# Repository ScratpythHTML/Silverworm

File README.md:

# Silverworm
Hardware and software design for the Silverworm spiral yarn wrapping machine.

## Group A
This is the wrapping team. We have designed a rotating arm that enscapulates a core yarn with a conductive outer fibre. The code in this repository is used to set the speed of the motor.

### Hardware
- Arduino Nano Every
- VNH5019 Motor Driver
- Honeywell Digital Hall Effect Sensor
- CHANCS 30W Permanent Magnet DC Motor 

### Software
The arduino code takes an inputted reference speed and accelerates the motor to this. It uses a Hall effect sensor and magnets on the arm to calculate the current speed. A PID controller is used for this system to eliminate error and ensure the motor willl get to the correct speed with in a set time. 

## Group B
This is the feeding. We have a feeding system that is passively tensioned which goes into team A's system; after the warpped yarn comes out, we collect it on a rotating collecting spool, which is on a linear rail to ensure orthodirectionality. 

### Hardware
- STM32
- DM423T Stepper Driver
- Linear Guide Rail with Nema 23 Stepper Motor
- oDrive S1 Motor Driver
- 24V 3000RPM 0.16Nm 50W 3.30A 42x42x62mm Brushless DC Motor ( with included hall effect sensor ) 
- 2 x Incremental Rotary Encoder IHC3808-001G-2000BZ1 ABZ 3-Channel 8mm Hollow Shaft

### Software
The code would take a inputted speed of the linear core yarn and then calculate the corresponding speeds that the linear rail and the BLDC motor would need to run at to ensure linear speed is accurate. The 2 encoders would give us both the radial velocity of the wrapper and the core yarn, allowing us to create a closed-loop control.

## Group C
This is the integration & control software — a PyQt6 app on a Raspberry Pi that reads the physical control panel, drives both motors, and measures yarn pitch live from a microscope camera.

### Hardware
- Raspberry Pi (Compute Module 5 + IO board)
- ESP32 physical UI panel — dials + mode/power switches (I2C)
- Wrap & feed motor controllers (SPI)
- AmScope HHD 8300-P USB microscope

### Software
The app is the system's central controller. It holds the machine state (mode, power, wrap + feed speeds), and the **physical panel is always the source of truth** — GUI controls are overwritten by the next dial/switch input. In AUTO it measures wrap pitch from the live camera and adjusts feed speed to hit the target; in MANUAL it overlays the target pitch/angle on the camera view for hand setup.

### Quick start

**On the wrapping machine (Raspberry Pi):**
```bash
python3 -m pip install -r interface/requirements-rpi.txt --break-system-packages
cd interface && python3 app.py
```

**On another computer (development, no hardware):**
```bash
python3 -m pip install -r interface/requirements.txt
cd interface && python3 app.py
```

On first launch you'll set target pitch, wire thickness, and tube diameter (tick "Remember settings" to skip it next time). With no panel attached, use the **Debug** menu to simulate dial/switch input.

### Code files
```
interface/
  app.py             Launcher — startup dialog → main window
  ui/main_window.py  Wires UI + state + hardware together
  app_state.py       Central state (mode/power/speeds), routes motor commands
  config.py          Settings, JSON persistence, wrap-angle math
  pitch_control.py   Closed-loop pitch → feed-speed control
  telemetry.py       Per-command timing/telemetry for the test report
  storage.py         Atomic saves (snapshots, recordings, logs)
  hardware.py        Picks real vs mock I2C/SPI transports per platform
  comms/
    pui.py           ESP32 panel protocol (I2C parser + listener)
    motor_spi.py     Arduino motor protocol (SPI packet codec)
  camera/            AmScope detection, capture, rolling frame buffer
  processing/
    pipeline.py      Runs pitch estimation on live camera frames
  ui/                GUI widgets (camera view, controls, graphs, dialogs)
  hil_test.py        Hardware-in-the-loop harness (no camera needed)
  diagnose.py        Environment / setup checker
image-processing/
  pitch_estimate.py  CV pitch measurement (OpenCV + SciPy)
```

### Continuing development
Start at `app.py` → `ui/main_window.py` → `app_state.py` (the central state machine). The reference sections below cover the protocols, formulas, and extension recipes you need to add features or bring up new hardware.

## How it works (reference)

### Architecture
```
ESP32 (panel) ──I2C──► Raspberry Pi (this app) ──SPI──► Arduino (motors)
 dials/switches          PyQt6 GUI + vision            wrap + feed
                         AppState = source of truth
```
The **physical panel always wins**: any dial/switch event overwrites what the GUI set. The GUI is a display/backup.

### Communication protocols
**I2C — panel → Pi (ASCII):**

| Message | Meaning |
|---|---|
| `D1±N` | Dial 1 (wrap) ± N detents, N∈{1,2,3} = small/med/large |
| `D2±N` | Dial 2 (feed) ± N detents |
| `AS0` / `AS1` | Mode → MANUAL / AUTO |
| `TP` | Toggle machine power |

Dials send *increments*, not absolute values; the detent→units lookup is in `DetentConfig` (`config.py`).

**SPI — Pi → Arduino (byte packets):**

| Prefix | Command | Payload |
|--------|---------|---------|
| `0x01` | Start | speedL, speedH (uint16 LE) |
| `0x02` | Stop | stop_type (1=ramp, 2=emergency, 3=power-off) |
| `0x03` | Set speed | speedL, speedH |
| `0x04` | Test movement | movement_type |
| `0x05` | Request speed | — |

**SPI — Arduino → Pi:** `0x01` current speed · `0x02` error_code · `0x03` sequence status.

### Core formulas
```python
theta = arctan(pitch / (pi * (tube_diameter + 2 * wire_thickness)))  # wrap angle
pitches_um = np.diff(peak_positions_px) * um_per_px                   # pitch from peaks
cv = std_pitch / mean_pitch                                          # confidence:
#   HIGH if wraps>=10 and cv<0.20 ; MEDIUM if wraps>=5 and cv<0.35 ; else LOW
```

### Settings
Persisted to the OS config dir, loaded on startup (target pitch, wire thickness, tube diameter, detent→speed mappings, remember-settings): macOS `~/Library/Preferences/Silverworm/config.json`, Linux `~/.config/Silverworm/config.json`. The manual-mode GUI toggle is hidden by default (enable in Settings with the warning ack) to avoid PUI/GUI desync.

## Extending the app
- **New PUI message:** add a case in `parse_pui_message()` + a dataclass (`comms/pui.py`) → signal on `PUIListener` → `apply_*` handler on `AppState` → wire in `MainWindow._connect_app_state_signals()` → test in `tests/test_pui_protocol.py` + `tests/test_app_state.py`.
- **New motor command:** add to `CommandPrefix` + `build_<cmd>()` with bounds checks (`comms/motor_spi.py`) → method on `MotorController` → test in `tests/test_motor_spi.py`.
- **Tune pitch detection:** edit `image-processing/pitch_estimate.py` (`min_dist_px`, `sigma`, `prom_factor`).

## Testing
```bash
cd interface
pytest -q tests/test_pui_protocol.py tests/test_motor_spi.py tests/test_app_state.py
```
The protocol layer is fully tested without hardware via `MockPUITransport` / `MockSPITransport`. Camera/UI tests need Linux + `pytest-qt`.

## Repository map
Several subfolders have their own README with hardware-specific detail (pin maps, wiring, board files). Start here, then drill in:

| Folder | Contents |
|--------|----------|
| [interface/](interface/) | Group C control software (see above) |
| [image-processing/](image-processing/) | Pitch-measurement CV pipeline |
| [GroupA/](GroupA/) | Group A wrapper-motor firmware (Arduino Nano Every) |
| [GroupB/](GroupB/README.md) | Group B collecting firmware + Uno pin map |
| [IO Panel/](IO%20Panel/Silverworm_Control_Panel/README.md) | ESP32 panel pinout + I2C protocol |
| → [Web test tool](IO%20Panel/Silverworm_Control_Panel/IO%20Panel%20Software/Web_Test_Version/README.md) | Browser serial test UI for the panel |
| [Motherboard/Hardware/](Motherboard/Hardware/Silverworm%20-%20CM5%20Motherboard/) | CM5 carrier-board KiCAD files |
| [Motherboard/Software/](Motherboard/Software/README.md) | Enabling SPI/I2C on the CM5 |
| [Subsystem Interfacing/](Subsystem%20Interfacing/README.md) | Cross-board SPI wiring overview |

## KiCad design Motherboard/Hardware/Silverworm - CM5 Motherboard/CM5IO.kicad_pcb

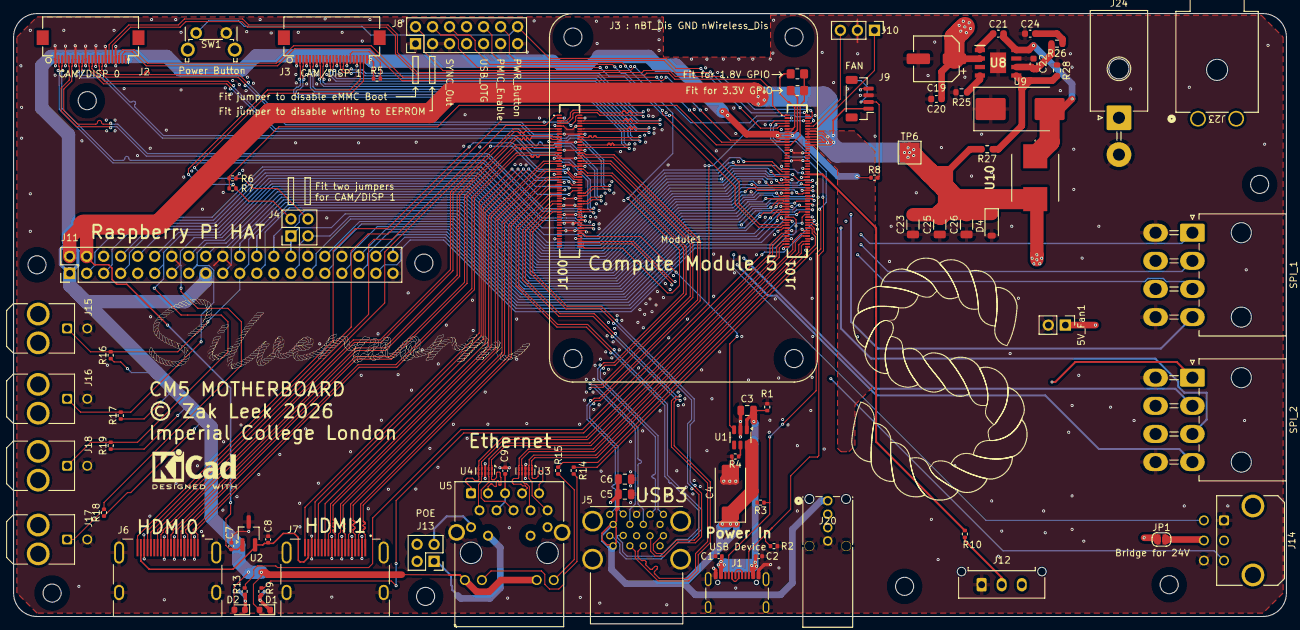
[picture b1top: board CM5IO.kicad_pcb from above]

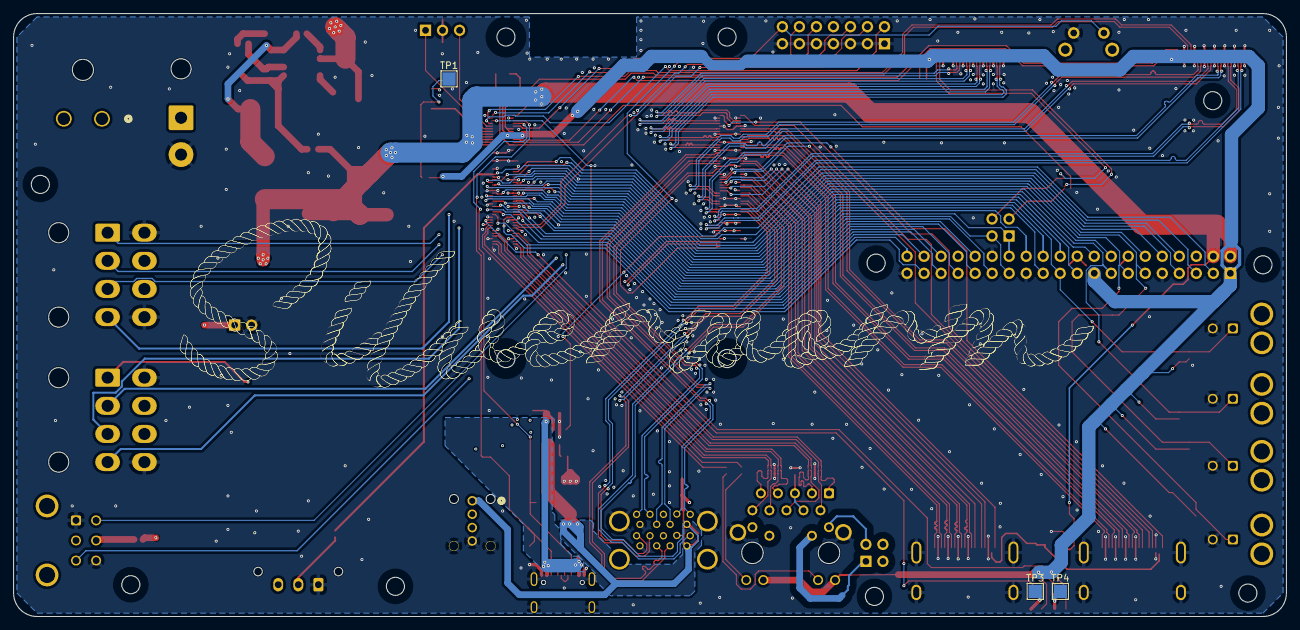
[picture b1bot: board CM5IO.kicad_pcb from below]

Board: 4 copper layers, 190.0 x 90.0 mm, 92 parts (3 on the bottom side), 148 nets.

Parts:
5V_Fan1: 1x2 Pin Header; PinHeader_1x02_P2.54mm_Vertical
C1, C2, C7, C8, C9: 100n; C_0402_1005Metric
C3, C5, C6: 10u; C_0805_2012Metric
C4: 100uF; CP_EIA-7343-31_Kemet-D
C19: GVT1J476M0608CNVC; CP_Elec_6.3x7.7
C20, C21: 100nF; C_0603_1608Metric
C22: 68pF; C_0603_1608Metric
C23, C25, C26: 47uF; C_1206_3216Metric
C24: 22nF; C_0603_1608Metric
D1: LED Green; LED_0603_1608Metric
D2: LED Red; LED_0603_1608Metric
D4: SMFJ5.0A; D_SOD-123
H1, H2, H3, H4, H5, H6, H7, H8: MountingHole; MountingHole_2.7mm_M2.5_DIN965
J1: USB_C_Receptacle_USB2.0; USB_C_Receptacle_GCT_USB4105-xx-A_16P_TopMnt_Horizontal
J2, J3: Conn_01x22_Female; Hirose_FH12-22S-0.5SH_1x22-1MP_P0.50mm_Horizontal
J4, J13: THD-02-R; PinHeader_2x02_P2.54mm_Vertical
J5: USB3_A; MTCONN_UBAF30-D2011
J6, J7: 690-019-298-412; EDAC 690-019-298-412
J8: Conn_02x07_Odd_Even; PinHeader_2x07_P2.54mm_Vertical
J9: JST_SHBM04B-SRSS-TB; JST_SH_BM04B-SRSS-TB_1x04-1MP_P1.00mm_Vertical
J10: Conn_01x03; PinHeader_1x03_P2.54mm_Vertical
J11: THD-20-R; PinHeader_2x20_P2.54mm_Vertical
J12: Microfit 3-pin; Molex_Micro-Fit_3.0_43650-0315_1x03_P3.00mm_Vertical
J14: Microfit 6-pin; Molex_Micro-Fit_3.0_43045-0621_2x03-1MP_P3.00mm_Horizontal
J15, J16, J17, J18: Microfit 2-Pin; Molex_Micro-Fit_3.0_43045-0221_2x01-1MP_P3.00mm_Horizontal
J20: USB_A; CONN_48204-0001_MOL
J23: Mega-Fit-1row-2pin; CONN_2002412000_02_MOL
J24: Mega-Fit-2row-2pin; Molex_Mega-Fit_76825-0002_2x01_P5.70mm_Horizontal
J100, J101: 101642271001A1RLF
JP1: Jumper_2_Open; SolderJumper-2_P1.3mm_Open_RoundedPad1.0x1.5mm
Module1: ComputeModule5-CM5; Raspberry-Pi-5-Compute-Module
R1, R5, R6, R7: 2.2K 1%; R_0402_1005Metric
R2, R3: 5.1K; R_0402_1005Metric
R4: 15K 1%; R_0402_1005Metric
R8: 10K 1%; R_0402_1005Metric
R9, R13: 1k; R_0402_1005Metric
R10, R14, R15: 470R; R_0402_1005Metric
R11: 0R; R_0805_2012Metric_Pad1.20x1.40mm_HandSolder
R12: nf; R_0805_2012Metric_Pad1.20x1.40mm_HandSolder
R16, R17, R18, R19: 10K; R_0402_1005Metric
R25: 120k; R_0603_1608Metric
R26, R28: 10k; R_0603_1608Metric
R27: 51k; R_0603_1608Metric
SPI_1, SPI_2: Minifit 2x4; Molex_Mini-Fit_Jr_5569-08A2_2x04_P4.20mm_Horizontal
SW1: Right angle Tact button; SW_Tactile_SPST_Angled_PTS645Vx58-2LFS
TP1, TP3, TP4: TestPoint; TestPoint_Pad_2.0x2.0mm
TP6: +5V; TestPoint_Pad_3.0x3.0mm
U1: AP22653W6; SOT-23-6
U2: RT9742SNGV; TSOT-23_HandSoldering
U3, U4: TPD4EUSB30; USON-10_2.5x1.0mm_P0.5mm
U5: MagJack-A70-112-331N126; TRJG0926HENL
U8: TPS54560DDAR; SOIC127P600X170-9N
U9: SS54; D_SMC_Handsoldering
U10: 10uH; ETQP5M_YFM

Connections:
24V_INPUT: J23.1, J24.1
+5V: 5V_Fan1.1, C1.1, C2.1, C3.1, C7.1, C23.2, C25.2, C26.2, D4.1 (K), J1.A4 (VBUS), J1.A9 (VBUS), J1.B4 (VBUS), J1.B9 (VBUS), J9.1, J11.2, J11.4, J12.3, J14.2, Module1.77 (+5v_(Input)), Module1.79 (+5v_(Input)), Module1.81 (+5v_(Input)), Module1.83 (+5v_(Input)), Module1.85 (+5v_(Input)), Module1.87 (+5v_(Input)), R1.2, R27.2, SPI_1.7, SPI_2.7, TP6.1, U1.1 (IN), U2.1 (IN), U10.2
+24V: C19.1, C20.1, J23.2, JP1.1 (A), SPI_1.6, SPI_2.6, U8.2 (VIN)
/+3.3v: D1.2 (A), D2.2 (A), J11.1, J11.17, Module1.84 (+3.3v_(Output)), Module1.86 (+3.3v_(Output)), R8.1, R11.1, R16.1, R17.1, R18.1, R19.1, U5.15 (LEDY_A), U5.17 (LEDG_A)
/CC1: J1.A5 (CC1), Module1.94 (CC1), R3.1
/CC2: J1.B5 (CC2), Module1.96 (CC2), R2.1
/CM5_GPIO ( Ethernet, GPIO, SDCARD)/+1.8v: Module1.88 (+1.8v_(Output)), Module1.90 (+1.8v_(Output)), R12.1
/CM5_GPIO ( Ethernet, GPIO, SDCARD)/BT_nDis: J10.3, Module1.91 (BT_nDisable)
/CM5_GPIO ( Ethernet, GPIO, SDCARD)/CAM_GPIO0: J2.17, Module1.97 (CAM_GPIO0)
/CM5_GPIO ( Ethernet, GPIO, SDCARD)/CAM_GPIO1: J2.18, Module1.100 (CAM_GPIO1)
/CM5_GPIO ( Ethernet, GPIO, SDCARD)/CSn_1: Module1.49 (GPIO18), SPI_1.4
/CM5_GPIO ( Ethernet, GPIO, SDCARD)/CSn_3: Module1.54 (GPIO4), SPI_2.4
/CM5_GPIO ( Ethernet, GPIO, SDCARD)/EEPROM_nWP: J8.4, Module1.20 (EEPROM_nWP)
/CM5_GPIO ( Ethernet, GPIO, SDCARD)/ETH_LEDG: Module1.17 (Ethernet_nLED2(3.3v)), R14.2
/CM5_GPIO ( Ethernet, GPIO, SDCARD)/ETH_LEDY: Module1.15 (Ethernet_nLED3(3.3v)), R15.2
/CM5_GPIO ( Ethernet, GPIO, SDCARD)/GPIO2: J11.3, Module1.58 (GPIO2)
/CM5_GPIO ( Ethernet, GPIO, SDCARD)/GPIO3: J11.5, Module1.56 (GPIO3)
/CM5_GPIO ( Ethernet, GPIO, SDCARD)/GPIO8: J11.24, Module1.39 (GPIO8)
/CM5_GPIO ( Ethernet, GPIO, SDCARD)/GPIO9: J11.21, J15.1, Module1.40 (GPIO9), R16.2
/CM5_GPIO ( Ethernet, GPIO, SDCARD)/GPIO10: J11.19, J14.4, Module1.44 (GPIO10)
/CM5_GPIO ( Ethernet, GPIO, SDCARD)/GPIO11: J11.23, J14.3, Module1.38 (GPIO11)
/CM5_GPIO ( Ethernet, GPIO, SDCARD)/GPIO12: J11.32, Module1.31 (GPIO12)
/CM5_GPIO ( Ethernet, GPIO, SDCARD)/GPIO13: J11.33, Module1.28 (GPIO13)
/CM5_GPIO ( Ethernet, GPIO, SDCARD)/GPIO15: J11.10, Module1.51 (GPIO15)
/CM5_GPIO ( Ethernet, GPIO, SDCARD)/GPIO16: J11.36, Module1.29 (GPIO16)
/CM5_GPIO ( Ethernet, GPIO, SDCARD)/GPIO23: J11.16, Module1.47 (GPIO23)
/CM5_GPIO ( Ethernet, GPIO, SDCARD)/GPIO24: J11.18, Module1.45 (GPIO24)
/CM5_GPIO ( Ethernet, GPIO, SDCARD)/GPIO25: J11.22, Module1.41 (GPIO25)
/CM5_GPIO ( Ethernet, GPIO, SDCARD)/GPIO26: J11.37, Module1.24 (GPIO26)
/CM5_GPIO ( Ethernet, GPIO, SDCARD)/GPIO_VREF: Module1.78 (GPIO_VREF(1.8v/3.3v_Input)), R6.1, R7.1, R11.2, R12.2
/CM5_GPIO ( Ethernet, GPIO, SDCARD)/ID_SC: J4.1, J11.28, Module1.35 (ID_SC)
/CM5_GPIO ( Ethernet, GPIO, SDCARD)/ID_SD: J4.3, J11.27, Module1.36 (ID_SD)
/CM5_GPIO ( Ethernet, GPIO, SDCARD)/LED_DATA: Module1.55 (GPIO14), R10.1
/CM5_GPIO ( Ethernet, GPIO, SDCARD)/LK_2: J16.1, Module1.46 (GPIO22), R17.2
/CM5_GPIO ( Ethernet, GPIO, SDCARD)/LK_3: J17.1, Module1.48 (GPIO27), R18.2
/CM5_GPIO ( Ethernet, GPIO, SDCARD)/LK_4: J18.1, Module1.50 (GPIO17), R19.2
/CM5_GPIO ( Ethernet, GPIO, SDCARD)/MISO_1: Module1.26 (GPIO19), SPI_1.2
/CM5_GPIO ( Ethernet, GPIO, SDCARD)/MISO_3: Module1.34 (GPIO5), SPI_2.2
/CM5_GPIO ( Ethernet, GPIO, SDCARD)/MOSI_1: Module1.27 (GPIO20), SPI_1.1
/CM5_GPIO ( Ethernet, GPIO, SDCARD)/MOSI_3: Module1.30 (GPIO6), SPI_2.1
/CM5_GPIO ( Ethernet, GPIO, SDCARD)/PMIC_ENABLE: J8.12, Module1.99 (PMIC_ENABLE)
/CM5_GPIO ( Ethernet, GPIO, SDCARD)/PWM: J9.2, Module1.19 (FAN_PWM), R8.2, TP1.1
/CM5_GPIO ( Ethernet, GPIO, SDCARD)/PWR_BUT: J8.14, Module1.92 (PWR_BUT), SW1.1
/CM5_GPIO ( Ethernet, GPIO, SDCARD)/SCLK_1: Module1.25 (GPIO21), SPI_1.3
/CM5_GPIO ( Ethernet, GPIO, SDCARD)/SCLK_3: Module1.37 (GPIO7), SPI_2.3
/CM5_GPIO ( Ethernet, GPIO, SDCARD)/SYNC_OUT: J8.6, Module1.18 (Ethernet_SYNC_OUT(3.3v))
/CM5_GPIO ( Ethernet, GPIO, SDCARD)/TACHO: J9.4, Module1.16 (FAN_TACHO)
/CM5_GPIO ( Ethernet, GPIO, SDCARD)/TR0_TAP: J13.3, U5.11 (VC1)
/CM5_GPIO ( Ethernet, GPIO, SDCARD)/TR1_TAP: J13.1, U5.12 (VC2)
/CM5_GPIO ( Ethernet, GPIO, SDCARD)/TR2_TAP: J13.2, U5.13 (VC3)
/CM5_GPIO ( Ethernet, GPIO, SDCARD)/TR3_TAP: J13.4, U5.14 (VC4)
/CM5_GPIO ( Ethernet, GPIO, SDCARD)/TRD0_N: Module1.10 (Ethernet_Pair0_N), U4.4 (D2+), U4.7, U5.2 (TRD0-)
/CM5_GPIO ( Ethernet, GPIO, SDCARD)/TRD0_P: Module1.12 (Ethernet_Pair0_P), U4.5 (D2-), U4.6, U5.1 (TRD0+)
/CM5_GPIO ( Ethernet, GPIO, SDCARD)/TRD1_N: Module1.6 (Ethernet_Pair1_N), U4.2 (D1-), U4.9, U5.6 (TRD1-)
/CM5_GPIO ( Ethernet, GPIO, SDCARD)/TRD1_P: Module1.4 (Ethernet_Pair1_P), U4.1 (D1+), U4.10, U5.3 (TRD1+)
/CM5_GPIO ( Ethernet, GPIO, SDCARD)/TRD2_N: Module1.9 (Ethernet_Pair2_N), U3.4 (D2+), U3.7, U5.8 (TRD2-)
/CM5_GPIO ( Ethernet, GPIO, SDCARD)/TRD2_P: Module1.11 (Ethernet_Pair2_P), U3.5 (D2-), U3.6, U5.7 (TRD2+)
/CM5_GPIO ( Ethernet, GPIO, SDCARD)/TRD3_N: Module1.5 (Ethernet_Pair3_N), U3.2 (D1-), U3.9, U5.10 (TRD3-)
/CM5_GPIO ( Ethernet, GPIO, SDCARD)/TRD3_P: Module1.3 (Ethernet_Pair3_P), U3.1 (D1+), U3.10, U5.9 (TRD3+)
/CM5_GPIO ( Ethernet, GPIO, SDCARD)/USBOTG: J8.10, Module1.101 (USB_OTG_ID)
/CM5_GPIO ( Ethernet, GPIO, SDCARD)/WL_nDis: J10.1, Module1.89 (WiFi_nDisable)
/CM5_GPIO ( Ethernet, GPIO, SDCARD)/nPWR_LED: Module1.95 (LED_nPWR), R13.2
/CM5_GPIO ( Ethernet, GPIO, SDCARD)/nRPIBOOT: J8.2, Module1.93 (nRPIBOOT)
/CM5_HighSpeed/+3.3v: J2.22, J3.22, R5.1
/CM5_HighSpeed/DPHY0_C_N: J2.8, Module1.127 (MIPI0_C_N)
/CM5_HighSpeed/DPHY0_C_P: J2.9, Module1.129 (MIPI0_C_P)
/CM5_HighSpeed/DPHY0_D0_N: J2.2, Module1.115 (MIPI0_D0_N)
/CM5_HighSpeed/DPHY0_D0_P: J2.3, Module1.117 (MIPI0_D0_P)
/CM5_HighSpeed/DPHY0_D1_N: J2.5, Module1.121 (MIPI0_D1_N)
/CM5_HighSpeed/DPHY0_D1_P: J2.6, Module1.123 (MIPI0_D1_P)
/CM5_HighSpeed/DPHY0_D2_N: J2.11, Module1.133 (MIPI0_D2_N)
/CM5_HighSpeed/DPHY0_D2_P: J2.12, Module1.135 (MIPI0_D2_P)
/CM5_HighSpeed/DPHY0_D3_N: J2.14, Module1.139 (MIPI0_D3_N)
/CM5_HighSpeed/DPHY0_D3_P: J2.15, Module1.141 (MIPI0_D3_P)
/CM5_HighSpeed/DPHY1_C_N: J3.8, Module1.187 (MIPI1_C_N)
/CM5_HighSpeed/DPHY1_C_P: J3.9, Module1.189 (MIPI1_C_P)
/CM5_HighSpeed/DPHY1_D0_N: J3.2, Module1.175 (MIPI1_D0_N)
/CM5_HighSpeed/DPHY1_D0_P: J3.3, Module1.177 (MIPI1_D0_P)
/CM5_HighSpeed/DPHY1_D1_N: J3.5, Module1.181 (MIPI1_D1_N)
/CM5_HighSpeed/DPHY1_D1_P: J3.6, Module1.183 (MIPI1_D1_P)
/CM5_HighSpeed/DPHY1_D2_N: J3.11, Module1.193 (MIPI1_D2_N)
/CM5_HighSpeed/DPHY1_D2_P: J3.12, Module1.195 (MIPI1_D2_P)
/CM5_HighSpeed/DPHY1_D3_N: J3.14, Module1.194 (MIPI1_D3_N)
/CM5_HighSpeed/DPHY1_D3_P: J3.15, Module1.196 (MIPI1_D3_P)
/CM5_HighSpeed/HDMI0_CEC: J6.13 (CEC), Module1.151 (HDMI0_CEC)
/CM5_HighSpeed/HDMI0_CK_N: J6.12 (CK-), Module1.190 (HDMI0_CLK_N)
/CM5_HighSpeed/HDMI0_CK_P: J6.10 (CK+), Module1.188 (HDMI0_CLK_P)
/CM5_HighSpeed/HDMI0_D0_N: J6.9 (D0-), Module1.184 (HDMI0_TX0_N)
/CM5_HighSpeed/HDMI0_D0_P: J6.7 (D0+), Module1.182 (HDMI0_TX0_P)
/CM5_HighSpeed/HDMI0_D1_N: J6.6 (D1-), Module1.178 (HDMI0_TX1_N)
/CM5_HighSpeed/HDMI0_D1_P: J6.4 (D1+), Module1.176 (HDMI0_TX1_P)
/CM5_HighSpeed/HDMI0_D2_N: J6.3 (D2-), Module1.172 (HDMI0_TX2_N)
/CM5_HighSpeed/HDMI0_D2_P: J6.1 (D2+), Module1.170 (HDMI0_TX2_P)
/CM5_HighSpeed/HDMI0_HOTPLUG: J6.19 (HPD/HEAC-), Module1.153 (HDMI0_HOTPLUG)
/CM5_HighSpeed/HDMI0_SCL: J6.15 (SCL), Module1.200 (HDMI0_SCL)
/CM5_HighSpeed/HDMI0_SDA: J6.16 (SDA), Module1.199 (HDMI0_SDA)
/CM5_HighSpeed/HDMI1_CEC: J7.13 (CEC), Module1.149 (HDMI1_CEC)
/CM5_HighSpeed/HDMI1_CK_N: J7.12 (CK-), Module1.166 (HDMI1_CLK_N)
/CM5_HighSpeed/HDMI1_CK_P: J7.10 (CK+), Module1.164 (HDMI1_CLK_P)
/CM5_HighSpeed/HDMI1_D0_N: J7.9 (D0-), Module1.160 (HDMI1_TX0_N)
/CM5_HighSpeed/HDMI1_D0_P: J7.7 (D0+), Module1.158 (HDMI1_TX0_P)
/CM5_HighSpeed/HDMI1_D1_N: J7.6 (D1-), Module1.154 (HDMI1_TX1_N)
/CM5_HighSpeed/HDMI1_D1_P: J7.4 (D1+), Module1.152 (HDMI1_TX1_P)
/CM5_HighSpeed/HDMI1_D2_N: J7.3 (D2-), Module1.148 (HDMI1_TX2_N)
/CM5_HighSpeed/HDMI1_D2_P: J7.1 (D2+), Module1.146 (HDMI1_TX2_P)
/CM5_HighSpeed/HDMI1_HOTPLUG: J7.19 (HPD/HEAC-), Module1.143 (HDMI1_HOTPLUG)
/CM5_HighSpeed/HDMI1_SCL: J7.15 (SCL), Module1.147 (HDMI1_SCL)
/CM5_HighSpeed/HDMI1_SDA: J7.16 (SDA), Module1.145 (HDMI1_SDA)
/CM5_HighSpeed/HDMI_5v: C8.1, J6.18 (+5V), J7.18 (+5V), U2.2 (OUT)
/CM5_HighSpeed/SCL0: J2.20, Module1.80 (SCL0)
/CM5_HighSpeed/SCL1: J3.20, J4.2, R7.2
/CM5_HighSpeed/SDA0: J2.21, Module1.82 (SDA0)
/CM5_HighSpeed/SDA1: J3.21, J4.4, R6.2
/CM5_HighSpeed/USB2_N: J20.2 (D-), Module1.103 (USB2_N)
/CM5_HighSpeed/USB2_P: J20.3 (D+), Module1.105 (USB2_P)
/CM5_HighSpeed/USB3-0-D_N: J5.A2 (D-), Module1.136 (USB3-0-D_N)
/CM5_HighSpeed/USB3-0-D_P: J5.A3 (D+), Module1.134 (USB3-0-D_P)
/CM5_HighSpeed/USB3-0-RX_N: J5.A6 (SSRX+), Module1.128 (USB3-0-RX_N)
/CM5_HighSpeed/USB3-0-RX_P: J5.A5 (SSRX-), Module1.130 (USB3-0-RX_P)
/CM5_HighSpeed/USB3-0-TX_N: J5.A9 (SSTX+), Module1.140 (USB3-0-TX_N)
/CM5_HighSpeed/USB3-0-TX_P: J5.A8 (SSTX-), Module1.142 (USB3-0-TX_P)
/CM5_HighSpeed/USB3-1-D_N: J5.B2 (D-), Module1.165 (USB3-1-D_N)
/CM5_HighSpeed/USB3-1-D_P: J5.B3 (D+), Module1.163 (USB3-1-D_P)
/CM5_HighSpeed/USB3-1-RX_N: J5.B6 (SSRX+), Module1.157 (USB3-1-RX_N)
/CM5_HighSpeed/USB3-1-RX_P: J5.B5 (SSRX-), Module1.159 (USB3-1-RX_P)
/CM5_HighSpeed/USB3-1-TX_N: J5.B9 (SSTX+), Module1.169 (USB3-1-TX_N)
/CM5_HighSpeed/USB3-1-TX_P: J5.B8 (SSTX-), Module1.171 (USB3-1-TX_P)
/CM5_HighSpeed/VBUS_EN: Module1.111 (VBUS_EN), U1.3 (EN)
GND: 5V_Fan1.2, C1.2, C2.2, C3.2, C4.2, C5.2, C6.2, C7.2, C8.2, C9.2, C19.2, C20.2, C22.1, C23.1, C24.1, C25.1, C26.1, D4.2 (A), J1.A1 (GND), J1.A12 (GND), J1.B1 (GND), J1.B12 (GND), J1.S1 (SHIELD), J2.1, J2.4, J2.7, J2.10, J2.13, J2.16, J2.19, J3.1, J3.4, J3.7, J3.10, J3.13, J3.16, J3.19, J5.10 (SHIELD), J5.A4 (GND), J5.A7 (DRAIN), J5.B4 (GND), J5.B7 (DRAIN), J6.2 (D2S), J6.5 (D1S), J6.8 (D0S), J6.11 (CKS), J6.17 (GND), J6.SH1 (SH), J6.SH2 (SH), J6.SH3 (SH), J6.SH4 (SH), J7.2 (D2S), J7.5 (D1S), J7.8 (D0S), J7.11 (CKS), J7.17 (GND), J7.SH1 (SH), J7.SH2 (SH), J7.SH3 (SH), J7.SH4 (SH), J8.1, J8.3, J8.5, J8.7, J8.9, J8.11, J8.13, J9.3, J10.2, J11.6, J11.9, J11.14, J11.20, J11.25, J11.30, J11.34, J11.39, J12.1, J14.1, J14.6, J15.2, J16.2, J17.2, J18.2, J20.4 (GND), J20.5 (Shield), J24.2, Module1.1 (GND), Module1.2 (GND), Module1.7 (GND), Module1.8 (GND), Module1.13 (GND), Module1.14 (GND), Module1.22 (GND), Module1.23 (GND), Module1.32 (GND), Module1.33 (GND), Module1.42 (GND), Module1.43 (GND), Module1.52 (GND), Module1.53 (GND), Module1.59 (GND), Module1.60 (GND), Module1.65 (GND), Module1.66 (GND), Module1.71 (GND), Module1.74 (GND), Module1.98 (GND), Module1.107 (GND), Module1.108 (GND), Module1.113 (GND), Module1.114 (GND), Module1.119 (GND), Module1.120 (GND), Module1.125 (GND), Module1.126 (GND), Module1.131 (GND), Module1.132 (GND), Module1.137 (GND), Module1.138 (GND), Module1.144 (GND), Module1.150 (GND), Module1.155 (GND), Module1.156 (GND), Module1.161 (GND), Module1.162 (GND), Module1.167 (GND), Module1.168 (GND), Module1.173 (GND), Module1.174 (GND), Module1.179 (GND), Module1.180 (GND), Module1.185 (GND), Module1.186 (GND), Module1.191 (GND), Module1.192 (GND), Module1.197 (GND), Module1.198 (GND), R1.1, R2.2, R3.2, R4.2, R25.1, R28.1, SPI_1.5, SPI_1.8, SPI_2.5, SPI_2.8, SW1.2, U1.2 (GND), U2.3 (GND), U3.3 (GND), U3.8 (GND), U4.3 (GND), U4.8 (GND), U5.19 (SHIELD), U5.20 (SHIELD), U8.7 (GND), U8.9 (EP), U9.1 (A)
unnamed: C9.1, U5.4 (CT), U5.5 (CT)
unnamed: C24.2, R26.1
unnamed: D1.1 (K), R9.1, TP3.1
unnamed: D2.1 (K), R13.1, TP4.1
unnamed: J1.A6 (D+), J1.B6 (D+)
unnamed: J1.A7 (D-), J1.B7 (D-)
unnamed: J3.17, R5.2
unnamed: J12.2, R10.2
unnamed: J14.5, JP1.2 (B)
unnamed: Module1.21 (LED_nACT), R9.2
unnamed: R4.1, U1.5 (ILIM)
unnamed: R15.1, U5.18 (LEDG_K)
unnamed: R14.1, U5.16 (LEDY_K)
unnamed: C21.1, U8.1 (BOOT)
unnamed: C22.2, R26.2, U8.6 (COMP)
unnamed: R27.1, R28.2, U8.5 (FB)
unnamed: R25.2, U8.4 (RT/CLK)
unnamed: C21.2, U8.8 (SW), U9.2 (K), U10.1
VBUS: C4.1, C5.1, C6.1, J5.A1 (VBUS), J5.B1 (VBUS), J20.1 (VBUS), U1.6 (OUT)

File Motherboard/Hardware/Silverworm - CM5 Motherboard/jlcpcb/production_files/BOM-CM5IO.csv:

Comment,Designator,Footprint,LCSC,Quantity
100nF,"C20,C21",C_0603_1608Metric,C282519,2
101642271001A1RLF,"J100,J101",101642271001A1RLF,C6782225,2
10k,"R26,R28",R_0603_1608Metric,C25804,2
10uH,U10,ETQP5M_YFM,C2827354,1
120k,R25,R_0603_1608Metric,C25808,1
22nF,C24,C_0603_1608Metric,C21122,1
47uF,"C23,C25,C26",C_1206_3216Metric,C5448950,3
51k,R27,R_0603_1608Metric,C23196,1
68pF,C22,C_0603_1608Metric,C28262,1
GVT1J476M0608CNVC,C19,CP_Elec_6.3x7.7,C2983409,1
SMFJ5.0A,D4,D_SOD-123,C5380699,1
SS54,U9,D_SMC_Handsoldering,C7420369,1
TPS54560DDAR,U8,SOIC127P600X170-9N,C31966,1
470R,R14,R_0402_1005Metric,,1
1k,R13,R_0402_1005Metric,,1
0R,R11,R_0805_2012Metric_Pad1.20x1.40mm_HandSolder,,1
10K 1%,R8,R_0402_1005Metric,,1
2.2K 1%,R5,R_0402_1005Metric,,1
15K 1%,R4,R_0402_1005Metric,,1
5.1K,R3,R_0402_1005Metric,,1
5.1K,R2,R_0402_1005Metric,,1
100n,C8,C_0402_1005Metric,,1
100n,C7,C_0402_1005Metric,,1
100n,C1,C_0402_1005Metric,,1
10u,C3,C_0805_2012Metric,,1
100n,C2,C_0402_1005Metric,,1
10K,R17,R_0402_1005Metric,,1
10K,R16,R_0402_1005Metric,,1
470R,R15,R_0402_1005Metric,,1
1k,R9,R_0402_1005Metric,,1
10u,C6,C_0805_2012Metric,,1
10u,C5,C_0805_2012Metric,,1
100uF,C4,CP_EIA-7343-31_Kemet-D,,1
10K,R19,R_0402_1005Metric,,1
10K,R18,R_0402_1005Metric,,1
1x2 Pin Header,5V_Fan1,PinHeader_1x02_P2.54mm_Vertical,,1
Conn_01x22_Female,J2,Hirose_FH12-22S-0.5SH_1x22-1MP_P0.50mm_Horizontal,,1
Conn_01x22_Female,J3,Hirose_FH12-22S-0.5SH_1x22-1MP_P0.50mm_Horizontal,,1
470R,R10,R_0402_1005Metric,,1
TPD4EUSB30,U3,USON-10_2.5x1.0mm_P0.5mm,,1
RT9742SNGV,U2,TSOT-23_HandSoldering,,1
THD-20-R,J11,PinHeader_2x20_P2.54mm_Vertical,,1
LED Red,D2,LED_0603_1608Metric,,1
THD-02-R,J13,PinHeader_2x02_P2.54mm_Vertical,,1
USB_C_Receptacle_USB2.0,J1,USB_C_Receptacle_GCT_USB4105-xx-A_16P_TopMnt_Horizontal,,1
LED Green,D1,LED_0603_1608Metric,,1
2.2K 1%,R1,R_0402_1005Metric,,1
MagJack-A70-112-331N126,U5,TRJG0926HENL,,1
690-019-298-412,J7,EDAC 690-019-298-412,,1
690-019-298-412,J6,EDAC 690-019-298-412,,1
THD-02-R,J4,PinHeader_2x02_P2.54mm_Vertical,,1
2.2K 1%,R6,R_0402_1005Metric,,1
2.2K 1%,R7,R_0402_1005Metric,,1
TPD4EUSB30,U4,USON-10_2.5x1.0mm_P0.5mm,,1
Conn_02x07_Odd_Even,J8,PinHeader_2x07_P2.54mm_Vertical,,1
USB3_A,J5,MTCONN_UBAF30-D2011,,1
JST_SHBM04B-SRSS-TB,J9,JST_SH_BM04B-SRSS-TB_1x04-1MP_P1.00mm_Vertical,,1
AP22653W6,U1,SOT-23-6,,1
Right angle Tact button,SW1,SW_Tactile_SPST_Angled_PTS645Vx58-2LFS,,1
100n,C9,C_0402_1005Metric,,1

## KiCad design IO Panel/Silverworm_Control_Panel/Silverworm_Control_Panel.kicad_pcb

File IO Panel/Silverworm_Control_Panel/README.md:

# UI Panel Pinout

| Pin     | Use      | Mode         |
|---------|----------|--------------|
| GPIO 0  | LED1-R   | ANALOG OUT   |
| GPIO 1  | LED1-G   | ANALOG OUT   |
| GPIO 2  | LED1-B   | ANALOG OUT   |
| GPIO 3  | TOGGLE   | DIG INPUT    |
| GPIO 13 | BTN2_LED | NOT USED     |
| GPIO 14 | BTN_1LED | DIGITAL OUT  |
| GPIO 4  | BTN2     | NOT USED     |
| GPIO 5  | BTN1     | INPUT PULLUP |
| GPIO 24 | DIAL1A   | DIG INPUT    |
| GPIO 23 | DIAL1B   | DIG INPUT    |
| GPIO 10 | DIAL1NO  | INPUT PULLUP |
| GPIO 11 | DIAL2A   | DIG INPUT    |
| GPIO 25 | DIAL2B   | DIG INPUT    |
| GPIO 12 | DIAL2NO  | INPUT PULLUP |
| GPIO 8  | SDA      | SDA          |
| GPIO 22 | SCL      | SCL          |
| GPIO 9  | LED2-R   | ANALOG OUT   |
| GPIO 27 | LED2-G   | ANALOG OUT   |
| GPIO 26 | LED2-B   | ANALOG OUT   |

# UI Panel Communications Protocol:

Uses I2C for communications between the ESP32 and the RPi

On the RPi side, we are using pins:
GPIO10 for SDA
GPIO11 for SCL

## I2C Functions for Communication:

The ESP32 sends the change in speeds for the motors, which the Raspberry Pi then applies to the variables within the backend which store the target motor speeds

### For Dials:
The ESP32 sends the label `D1` or `D2` before every command to identify dials 1 and 2
Then the number that it increments by:
- Small detent gives a `+1` or `-1`
- Medium detent gives `+2` or `-2`
- Large detent gives `+3` or `-3`

_For example: `D1-2` or `D2+1`_

So the ESP32 tells the RPi _which_ detent option is being used, it is then up to the RPi to decide what this means with regards to motor speeds.
The user can decide what the increments are for each motor/dial combo.

### For the auto/manual switch:
The ESP32 sends the label `AS` before the argument
- It sends `0` if it is set to manual mode
- It sends `1` if it is set to automatic mode

So as soon as the RPi receives `AS0`, it sets the program to manual, regardless of what is already running on the machine. As soon as the RPi receives `AS1` it goes to automatic mode. The GUI still has the power to change the mode, but the signals received from the ESP32 always override the mode.

### For the ON/OFF switch:
The ESP sends a simple command `TP` which toggles the machine between the ON and OFF state.
The RPi sends `ON` or `OFF` to the ESP32 when it the machine starts and stops, so that the ESP can cotnrol the status light inside the power button.

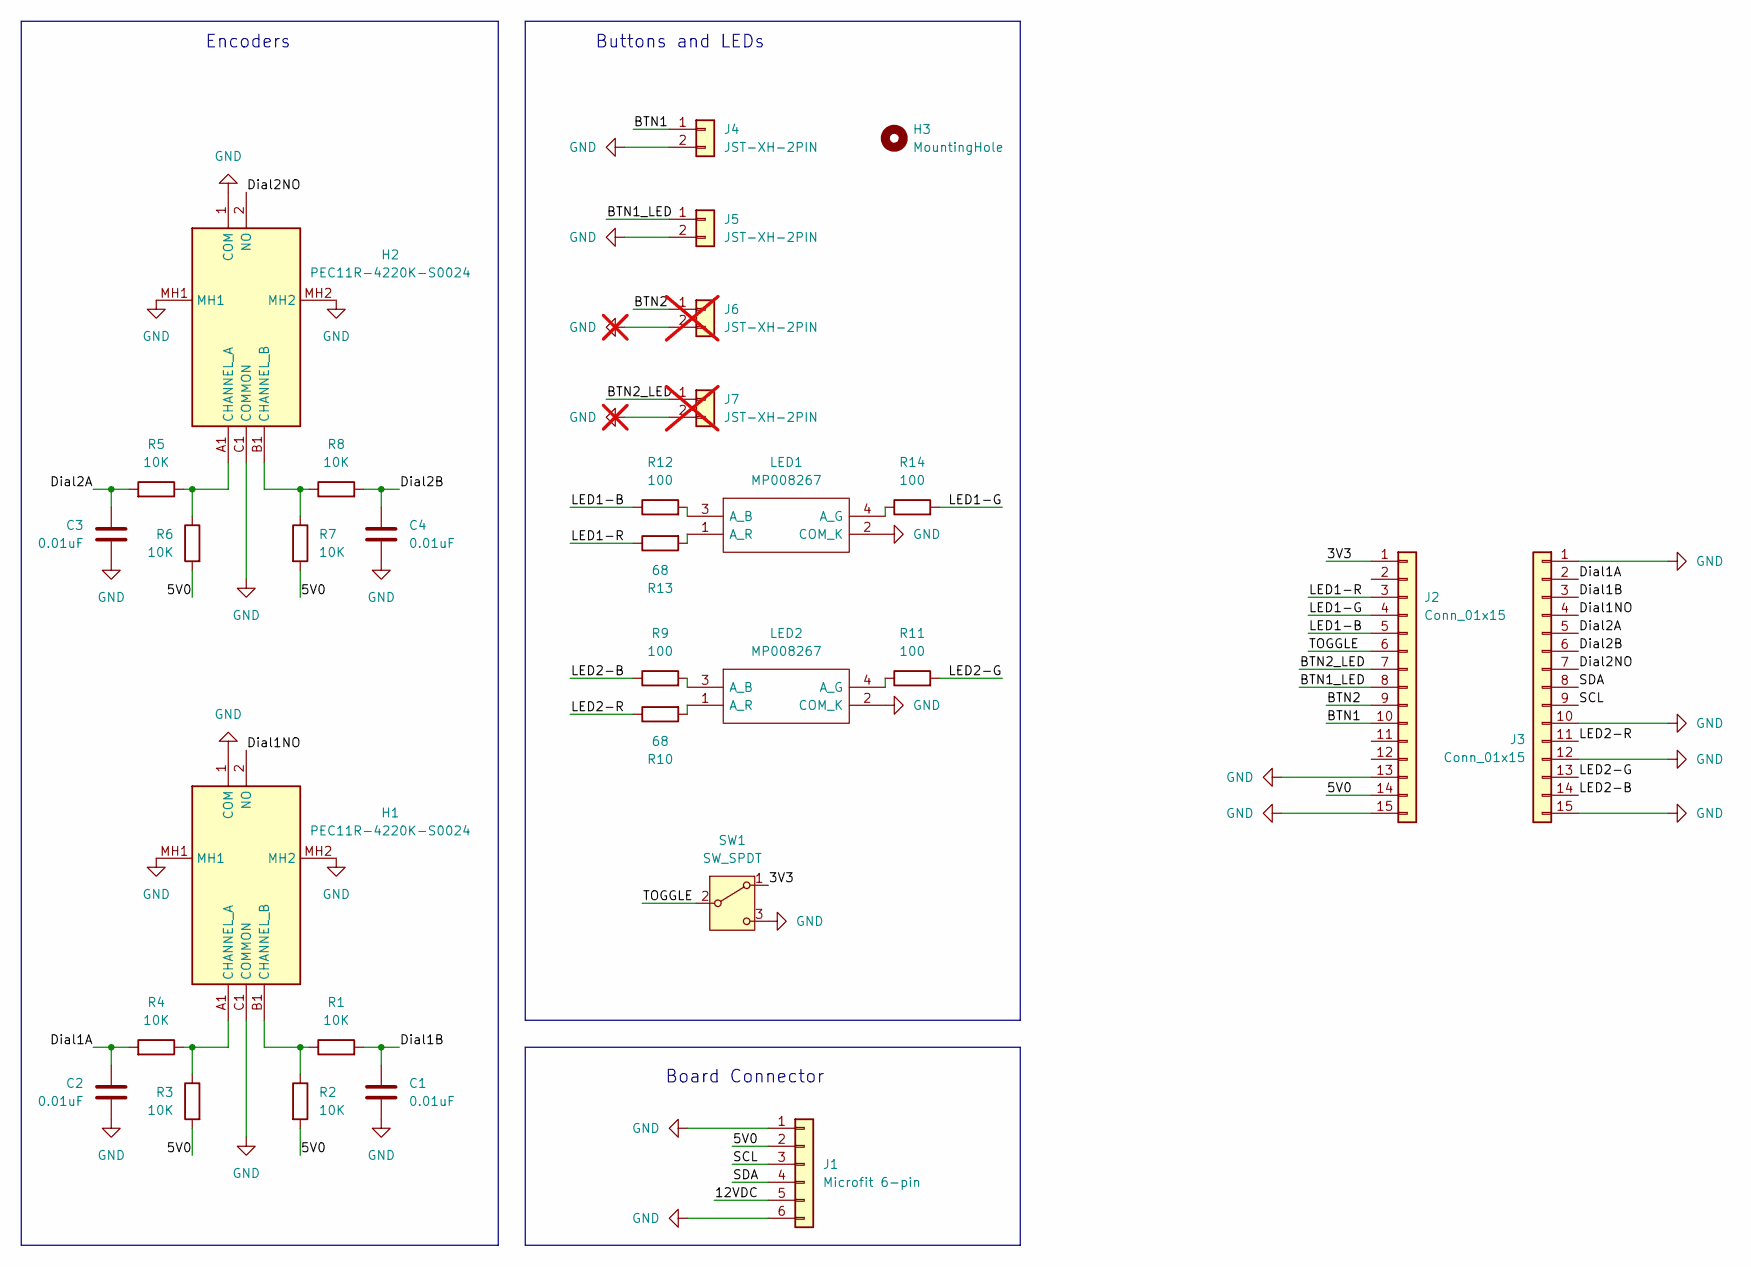
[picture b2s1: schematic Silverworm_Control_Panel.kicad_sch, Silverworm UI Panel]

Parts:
C1, C2, C3, C4: 0.01uF; CP_EIA-1608-10_AVX-L
H1, H2: PEC11R-4220K-S0024; PEC11R4220KS0024; Manufacturer_Part_Number PEC11R-4220K-S0024
H3: MountingHole; MountingHole_17mm_Pad_TopBottom
J1: Microfit 6-pin; Molex_Micro-Fit_3.0_43045-0621_2x03-1MP_P3.00mm_Horizontal; Manufacturer_Part_Number 430450621
J2, J3: Conn_01x15; PinSocket_1x15_P2.54mm_Vertical; Manufacturer_Part_Number M20-7821546
J4, J5: JST-XH-2PIN; Manufacturer_Part_Number B2B-XH-A(LF)(SN)
J6, J7: JST-XH-2PIN; Manufacturer_Part_Number B2B-XH-A(LF)(SN); not fitted
LED1, LED2: MP008267; Manufacturer_Part_Number MP008267
R1, R2, R3, R4, R5, R6, R7, R8: 10K; R_0603_1608Metric_Pad0.98x0.95mm_HandSolder
R9, R11, R12, R14: 100; R_0603_1608Metric_Pad0.98x0.95mm_HandSolder
R10, R13: 68; R_0603_1608Metric_Pad0.98x0.95mm_HandSolder
SW1: SW_SPDT; HDRV3W51P470X254_1X3_813X508X2100P; Manufacturer_Part_Number 200MSP1T1B2M2QE

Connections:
/3V3: J2.1, SW1.1 (A); also elsewhere on the board
/5V0: J1.2, J2.14, R2.2, R3.2, R6.2, R7.2; also elsewhere on the board
/12VDC: J1.5
/BTN1: J2.10, J4.1
/BTN1_LED: J2.8, J5.1
/BTN2: J2.9, J6.1
/BTN2_LED: J2.7, J7.1
/Dial1A: C2.1, J3.2, R4.2
/Dial1B: C1.1, J3.3, R1.2
/Dial1NO: H1.2 (NO), J3.4
/Dial2A: C3.1, J3.5, R5.2
/Dial2B: C4.1, J3.6, R8.2
/Dial2NO: H2.2 (NO), J3.7
/LED1-B: J2.5, R12.1
/LED1-G: J2.4, R14.2
/LED1-R: J2.3, R13.1
/LED2-B: J3.14, R9.1
/LED2-G: J3.13, R11.2
/LED2-R: J3.11, R10.1
/SCL: J1.3, J3.9
/SDA: J1.4, J3.8
/TOGGLE: J2.6, SW1.2 (B)
GND: C1.2, C2.2, C3.2, C4.2, H1.1 (COM), H1.C1 (COMMON), H1.MH1, H1.MH2, H2.1 (COM), H2.C1 (COMMON), H2.MH1, H2.MH2, J1.1, J1.6, J2.13, J2.15, J3.1, J3.10, J3.12, J3.15, J4.2, J5.2, J6.2, J7.2, LED1.2 (COM_K), LED2.2 (COM_K), SW1.3 (C); also elsewhere on the board
unnamed: H1.A1 (CHANNEL_A), R3.1, R4.1
unnamed: H1.B1 (CHANNEL_B), R1.1, R2.1
unnamed: H2.A1 (CHANNEL_A), R5.1, R6.1
unnamed: H2.B1 (CHANNEL_B), R7.1, R8.1
unnamed: LED1.3 (A_B), R12.2
unnamed: LED1.4 (A_G), R14.1
unnamed: LED1.1 (A_R), R13.2
unnamed: LED2.3 (A_B), R9.2
unnamed: LED2.4 (A_G), R11.1
unnamed: LED2.1 (A_R), R10.2

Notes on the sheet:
Buttons and LEDs
Encoders
Board Connector

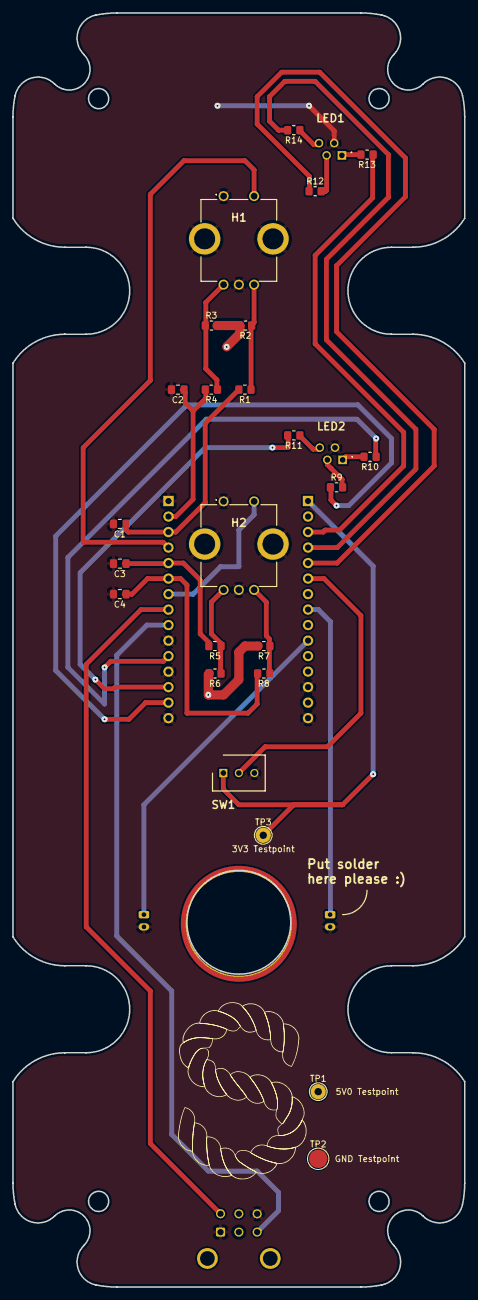
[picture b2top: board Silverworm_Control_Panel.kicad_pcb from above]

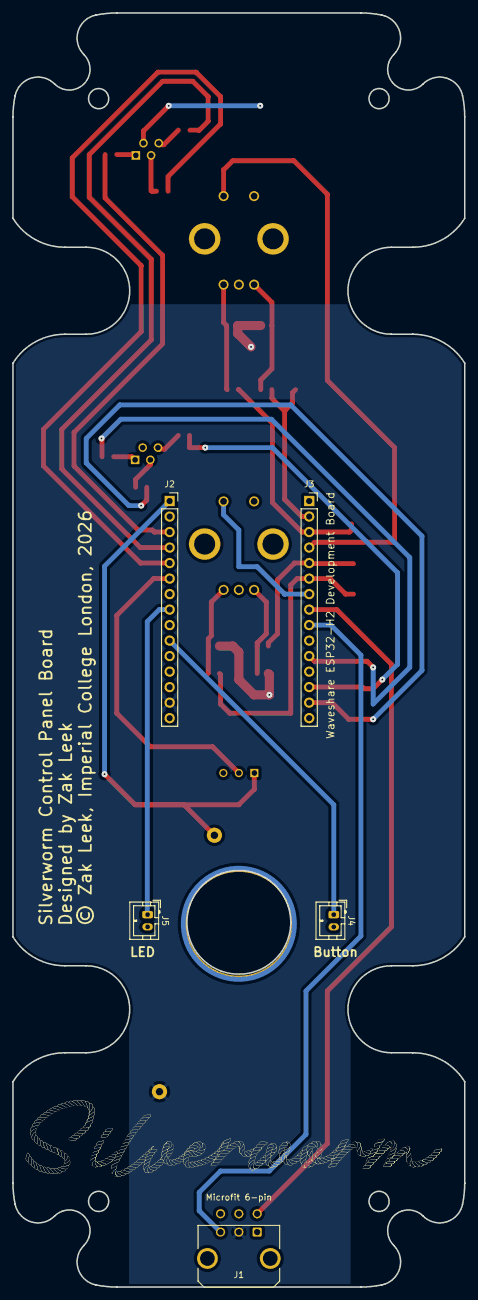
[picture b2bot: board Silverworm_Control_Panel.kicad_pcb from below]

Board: 2 copper layers, 74.0 x 208.7 mm, 32 parts (5 on the bottom side), 30 nets.

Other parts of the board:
TP1: 5V0 Testpoint; TestPoint_THTPad_D2.5mm_Drill1.2mm
TP2: GND Testpoint; TestPoint_Pad_D3.0mm
TP3: 3V3 Testpoint; TestPoint_THTPad_D2.5mm_Drill1.2mm

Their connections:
/3V3: TP3.1; also elsewhere on the board
/5V0: TP1.1; also elsewhere on the board
GND: TP2.1; also elsewhere on the board

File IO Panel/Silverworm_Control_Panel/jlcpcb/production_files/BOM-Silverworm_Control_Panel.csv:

Comment,Designator,Footprint,LCSC,Quantity
10K,R7,R_0805_2012Metric_Pad1.20x1.40mm_HandSolder,,1
0.01uF,C3,C_0805_2012Metric_Pad1.18x1.45mm_HandSolder,,1
10K,R6,R_0805_2012Metric_Pad1.20x1.40mm_HandSolder,,1
100,R14,R_0805_2012Metric_Pad1.20x1.40mm_HandSolder,,1
0.01uF,C4,C_0805_2012Metric_Pad1.18x1.45mm_HandSolder,,1
100,R11,R_0805_2012Metric_Pad1.20x1.40mm_HandSolder,,1
10K,R3,R_0805_2012Metric_Pad1.20x1.40mm_HandSolder,,1
68,R10,R_0805_2012Metric_Pad1.20x1.40mm_HandSolder,,1
10K,R5,R_0805_2012Metric_Pad1.20x1.40mm_HandSolder,,1
0.01uF,C2,C_0805_2012Metric_Pad1.18x1.45mm_HandSolder,,1
10K,R2,R_0805_2012Metric_Pad1.20x1.40mm_HandSolder,,1
10K,R8,R_0805_2012Metric_Pad1.20x1.40mm_HandSolder,,1
100,R12,R_0805_2012Metric_Pad1.20x1.40mm_HandSolder,,1
68,R13,R_0805_2012Metric_Pad1.20x1.40mm_HandSolder,,1
10K,R4,R_0805_2012Metric_Pad1.20x1.40mm_HandSolder,,1
0.01uF,C1,C_0805_2012Metric_Pad1.18x1.45mm_HandSolder,,1
100,R9,R_0805_2012Metric_Pad1.20x1.40mm_HandSolder,,1
10K,R1,R_0805_2012Metric_Pad1.20x1.40mm_HandSolder,,1

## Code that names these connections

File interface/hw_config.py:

"""
Raspberry Pi hardware pin configuration for the Silverworm system.

This file documents which physical pins are used on each platform and
what Linux device files they map to. Python opens device files — the
actual GPIO → peripheral mux is set by the OS via
/boot/firmware/config.txt (device-tree overlays).

IMPORTANT: GPIO10 and GPIO11 differ between platforms.
  - RPi 5 (test rig): GPIO10 = SPI0_MOSI, GPIO11 = SPI0_CLK  ← SPI, not I2C
  - CM5 (production):  GPIO10/11 *may* be reassigned to I2C via overlay
                       (not active/confirmed yet — see CM5Config below)

Do not use CM5Config until the CM5 board is available and the overlay
is verified.
"""

from __future__ import annotations

from dataclasses import dataclass


@dataclass(frozen=True)
class I2CConfig:
    """I2C bus configuration."""
    bus_number: int        # Linux /dev/i2c-N
    sda_gpio: int          # BCM GPIO number (documentation only)
    sda_physical_pin: int  # Physical board pin number
    scl_gpio: int
    scl_physical_pin: int
    pui_address: int = 0x55  # ESP32 I2C slave address (Control_panel.ino)


@dataclass(frozen=True)
class SPIConfig:
    """SPI bus + chip-select configuration for one motor controller."""
    bus: int               # Linux spidev bus number (B in /dev/spidev-B.D)
    device: int            # Chip-select index (D in /dev/spidev-B.D)
    mosi_gpio: int
    miso_gpio: int
    sclk_gpio: int
    cs_gpio: int
    max_speed_hz: int = 500_000
    mode: int = 0          # SPI Mode 0 (CPOL=0 CPHA=0) — Arduino default


@dataclass(frozen=True)
class PlatformConfig:
    name: str
    i2c: I2CConfig
    wrap_spi: SPIConfig    # Wrap motor (Arduino)
    feed_spi: SPIConfig    # Feed motor (Arduino)


# ---------------------------------------------------------------------------
# Raspberry Pi 5 — test rig configuration (active)
# ---------------------------------------------------------------------------
#
# I2C1: standard pins, always available, no overlay needed.
# SPI0: standard pins, enabled via raspi-config → Interfacing Options → SPI.
#   Wrap motor (Arduino) on SPI0 with chip-select CE0.
# SPI1: secondary bus, requires dtoverlay=spi1-1cs in /boot/firmware/config.txt.
#   Feed motor (Arduino) on SPI1 with chip-select CE0.
#
# Physical wiring reference:
#   I2C SDA  GPIO2   pin 3
#   I2C SCL  GPIO3   pin 5
#   SPI0 MOSI GPIO10  pin 19 ← wrap motor
#   SPI0 MISO GPIO9   pin 21
#   SPI0 SCLK GPIO11  pin 23
#   SPI0 CE0  GPIO7   pin 24
#   SPI1 MOSI GPIO20  pin 38 ← feed motor
#   SPI1 MISO GPIO19  pin 35
#   SPI1 SCLK GPIO21  pin 40
#   SPI1 CE0  GPIO18  pin 12

RPI5 = PlatformConfig(
    name="rpi5",
    i2c=I2CConfig(
        bus_number=1,
        sda_gpio=2,          sda_physical_pin=3,
        scl_gpio=3,          scl_physical_pin=5,
    ),
    wrap_spi=SPIConfig(
        bus=1, device=2,
        mosi_gpio=20,
        miso_gpio=19,
        sclk_gpio=21,
        cs_gpio=16,
    ),
    feed_spi=SPIConfig(
        bus=1, device=0,
        mosi_gpio=20,
        miso_gpio=19,
        sclk_gpio=21,
        cs_gpio=18,
    ),
)

# ---------------------------------------------------------------------------
# CM5 — FUTURE / NOT ACTIVE
# ---------------------------------------------------------------------------
#
# The CM5 carrier board routes I2C to GPIO10/11 via a device-tree overlay.
# That GPIO assignment conflicts with SPI0 on a standard Pi — the overlay
# must be confirmed before these numbers are usable.
#
# TODO (CM5 bring-up): verify the overlay bus number by running
#   ls /dev/i2c-*   after booting the CM5 with the overlay applied.
#
# Leave CM5 = None so build_transports() raises clearly instead of
# silently using wrong bus numbers.

CM5 = None  # not ready — see above


# ---------------------------------------------------------------------------
# Registry
# ---------------------------------------------------------------------------

PLATFORMS: dict[str, PlatformConfig | None] = {
    "rpi5": RPI5,
    "cm5": CM5,
}


def get_platform(name: str) -> PlatformConfig:
    """Return the PlatformConfig for the given name, or raise."""
    name = name.lower()
    if name not in PLATFORMS:
        raise ValueError(
            f"Unknown hw_platform {name!r}. Known: {list(PLATFORMS)}"
        )
    config = PLATFORMS[name]
    if config is None:
        raise NotImplementedError(
            f"Platform {name!r} is defined but not yet configured. "
            "See hw_config.py for bring-up instructions."
        )
    return config

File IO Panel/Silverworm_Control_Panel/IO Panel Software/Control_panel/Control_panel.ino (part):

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const int LED2_B = 26;

// Buttons and Switches
const int BTN1 = 5;
const int BTN1_LED = 14;
const int TOGGLE = 3;

// Encoders
const int DIAL1A = 24;
const int DIAL1B = 23;
const int DIAL1_BTN = 10;

const int DIAL2A = 11;
const int DIAL2B = 25;
const int DIAL2_BTN = 12;

// I2C Configuration
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  delay(1000);

  // Initialize pins
  pinMode(BTN1, INPUT_PULLUP);
  pinMode(BTN1_LED, OUTPUT);
  digitalWrite(BTN1_LED, LOW);

  pinMode(TOGGLE, INPUT_PULLUP);

  pinMode(DIAL1A, INPUT);
  pinMode(DIAL1B, INPUT);
  pinMode(DIAL1_BTN, INPUT_PULLUP);

  pinMode(DIAL2A, INPUT);
  pinMode(DIAL2B, INPUT);
  pinMode(DIAL2_BTN, INPUT_PULLUP);

  // RGB LEDs
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

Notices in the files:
IO Panel/Silverworm_Control_Panel/Silverworm_Control_Panel.kicad_pcb:
© Zak Leek, Imperial College London, 2026
IO Panel/Silverworm_Control_Panel/Silverworm_Control_Panel.kicad_sch:
Copyright © Zak Leek, Imperial College London
Motherboard/Hardware/Silverworm - CM5 Motherboard/CM5IO.kicad_pcb:
© Zak Leek 2026
